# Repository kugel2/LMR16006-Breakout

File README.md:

# LMR16006-Breakout
Breakoutboard 21x21mm for LMR16006 60V buck converter.

**_Warning_: this board is not tested**

Datasheet: http://www.ti.com/lit/ds/symlink/lmr16006.pdf

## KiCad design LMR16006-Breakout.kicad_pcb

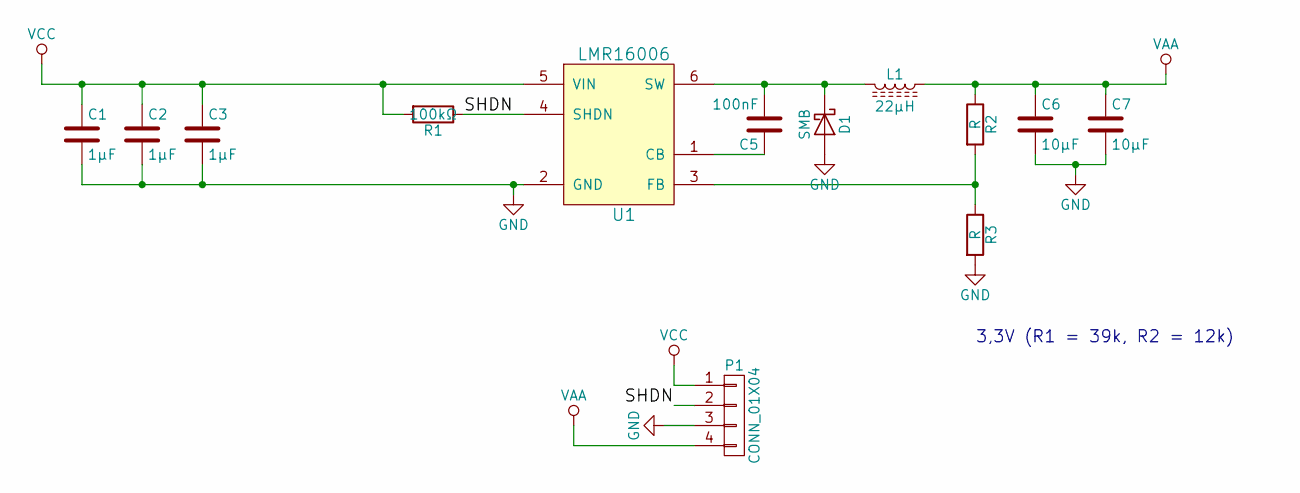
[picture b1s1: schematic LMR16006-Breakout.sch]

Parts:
C1, C2, C3: 1µF; C_1206
C5: 100nF; C_0805
C6, C7: 10µF; C_1206
D1: SMB; D_SMB_Standard
L1: 22µH
P1: CONN_01X04
R1: 100kΩ
R2, R3: R
U1: LMR16006

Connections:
/SHDN: P1.2, R1.1, U1.4 (SHDN)
GND: C1.2, C2.2, C3.2, C6.2, C7.2, D1.2 (A), P1.3, R3.2, U1.2 (GND)
unnamed: C5.1, U1.1 (CB)
unnamed: C5.2, D1.1 (K), L1.2, U1.6 (SW)
unnamed: R2.2, R3.1, U1.3 (FB)
VAA: C6.1, C7.1, L1.1, P1.4, R2.1
VCC: C1.1, C2.1, C3.1, P1.1, R1.2, U1.5 (VIN)

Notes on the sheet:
3,3V (R1 = 39k, R2 = 12k)

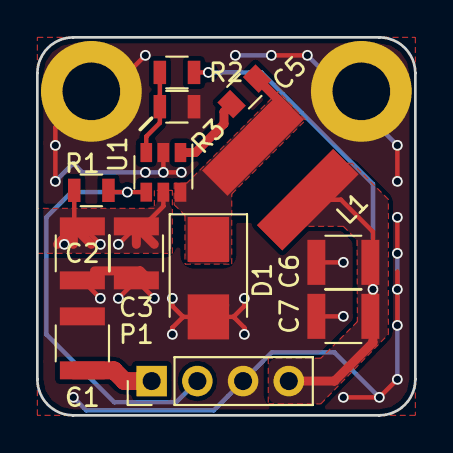
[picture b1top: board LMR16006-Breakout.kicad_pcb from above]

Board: 2 copper layers, 21.0 x 21.0 mm, 13 parts (0 on the bottom side), 7 nets.

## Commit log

2017-04-03 Update README.md
    add link to datasheet
2017-04-03 add .gitignore
2017-04-03 add schematics and layout
2017-04-03 added some GND vias
2017-04-03 some finetuning
2017-04-03 place silkscreen labels
2017-04-03 silkscreen description, oshw logo
2017-04-03 added 3d renderings from kicad
2017-04-03 smaller pictures
2017-04-03 Update README.md
    add some 3d renderings
2017-04-03 labels for pinheader
2017-04-07 change input and output capacitors from 1206 to 1210 footprints, change inductor from srn4026 to srn6045 footprint (to get Isat > 1.6A at 22µH)
2017-04-07 update 3d view, some tweaks, silkscreen
2017-04-09 silkscreen placement and text
2017-04-09 add gerber and pdf file
2017-04-09 update pictures
